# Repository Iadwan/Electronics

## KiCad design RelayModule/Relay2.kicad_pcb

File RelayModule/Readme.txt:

Relay Module designed by Ibrahim Aladwan inclduing KiCad files. 

This program is free software: you can redistribute it and/or modify it under the terms of the GNU General Public License as published by the Free Software Foundation, either version 3 of the License, or (at your option) any later version. This program is distributed in the hope that it will be useful, but WITHOUT ANY WARRANTY; without even the implied warranty of MERCHANTABILITY or FITNESS FOR A PARTICULAR PURPOSE. See the GNU General Public License for more details. You should have received a copy of the GNU General Public License along with this program. If not, see http://www.gnu.org/licenses/.

The Opinions Expressed In This Post Are My Own And Not Necessarily Those Of My Employer

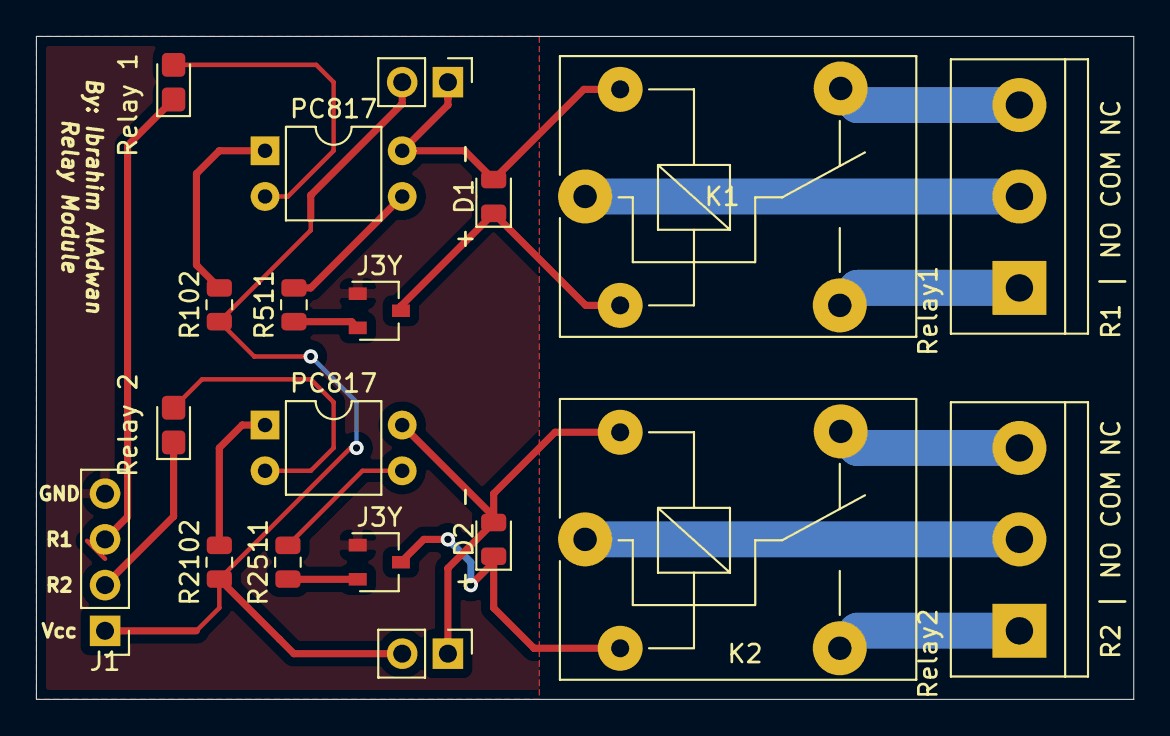
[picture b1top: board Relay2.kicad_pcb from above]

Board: 2 copper layers, 61.0 x 36.8 mm, 19 parts (0 on the bottom side), 22 nets.

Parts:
+ D1 -: D1; D_0805_2012Metric
+ D2 -: DIODE; D_0805_2012Metric
J1: PinHeader_1x04_P2.54mm_Vertical
J2: Conn_01x02; PinHeader_1x02_P2.54mm_Vertical
J3Y, J3Y#2: S8050; SOT-23W
Jumper1: PinHeader_1x02_P2.54mm_Vertical
K1, K2: Relay_SPDT_SANYOU_SRD_Series_Form_C
PC817, PC817#2: PC817; DIP-4_W7.62mm
R102, R2102: 1 k; R_0805_2012Metric
R511, R2511: 510 ohm; R_0805_2012Metric
Relay1: R1 | NO COM NC; TerminalBlock_bornier-3_P5.08mm
Relay2: R2 | NO COM NC; TerminalBlock_bornier-3_P5.08mm
Relay 1, Relay 2: LED; LED_0805_2012Metric_Castellated

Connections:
GNDREF: J1.4, J3Y.1, J3Y#2.1
unnamed: + D1 -.1, J3Y.3, K1.2
unnamed: + D1 -.2, Jumper1.1, K1.5, PC817.4
unnamed: J1.3, Relay 1.1
unnamed: PC817.2, Relay 1.2
unnamed: J1.2, Relay 2.1
unnamed: PC817#2.2, Relay 2.2
unnamed: + D2 -.1, J3Y#2.3, K2.2
unnamed: + D2 -.2, J2.1, K2.5, PC817#2.4
unnamed: J1.1, J2.2, Jumper1.2, R102.1, R2102.1
unnamed: J3Y.2, R511.1
unnamed: J3Y#2.2, R2511.1
unnamed: K1.1, Relay1.2
unnamed: K1.3, Relay1.1
unnamed: K1.4, Relay1.3
unnamed: K2.1, Relay2.2
unnamed: K2.3, Relay2.1
unnamed: K2.4, Relay2.3
unnamed: PC817#2.1, R2102.2
unnamed: PC817#2.3, R2511.2
unnamed: PC817.1, R102.2
unnamed: PC817.3, R511.2

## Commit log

2021-03-29 Add files via upload
    Version 1.1
